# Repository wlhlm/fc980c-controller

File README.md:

Leopold FC980C Replacement Controller
=====================================

This PCB replaces the controller of the Leopold FC980C keyboard to allow running
alternate firmware, especially open source firmware such as [QMK][QMK]. This
project relies heavily on the prior reverse engineering work done by hasu (aka
tmk) and collaborators.

This is the first PCB I have designed and as such I suspect this will have many
areas that can be improved. I am very much looking forward to hearing feedback
about this design, if you think something can be improved please open an issue
and let me know. I will list my reasons for various design choices below, as
well as an errata section to list shortcomings of the current design that I am
aware of.

(the resistor hand-soldered to the connector is due to a flaw of the revision 1
design, which has been fixed in revision 2)

**Specs:**
- STM32F401 MCU as found on the Blackpill boards
- Open Hardware licensed under CERN OHL-S v2
- designed to be assembled by [JLCPCB][JLC] (can of course be manufactured
  elsewhere, but board component selection has been optimized for JLC's
  component library)

**Why would anyone want a replacement keyboard controller for the FC980C?** In
case the original controller gets fried, the lack of controller replacement from
the manufacturer would otherwise mean tossing the whole (expensive) keyboard.
This board enables the usage of Free and Open Source firmware to replace the
proprietary stock firmware. Running alternate firmware allows enabling hardware
features not accessible through the original controller such as actuation point
adjustments, not to mention the plethora of software features enabled by QMK for
example.

[QMK]: https://qmk.fm/
[JLC]: https://jlcpcb.com/

Getting started
---------------

If you have received this controller fully assembled, your next step will be
firmware setup. Check the `firmware/` directory in this repository.

In case you still have to solder on the connectors, see the assembly section
below.

Assembly
--------

This PCB is intended to be manufactured and assembled by JLCPCB, **except** for
the connectors and a button on the back of the board, which most likely have to
be soldered on the PCB by hand.

The button (labled BOOT0) is through-hole and easily soldered by hand. Make sure
to place it on the bottom side, i.e. opposite side of the MCU, where the DIP
switches are on the original controller board.

The connector for the USB board (USB) is though-hole and can be hand-soldered.

The SWD header is optional and can be left unsoldered.

The connector labeled KEYBOARD is only available for surface mounting and
unfortunately not available at JLC for assembly (at least at the time of
design). Hand-soldering is a bit more challenging for this connector. Make sure
to use a healthy dose of flux and fine gauge solder wire.

Production
----------

While the PCB itself can be manufactured by a number of PCB houses, component
selection and SMD assembly is made with [JLCPCB][JLC] in mind. The
`jlcpcb/production_files` folder for each revision should include the necessary
BOM and CPL files in addition to the Gerbers. The board parameters are specified
in the PCB design file (the main parameters being a board thickness of 1.6mm and
2 copper layers). For the option "Remove Order Number", you can select "Specify
a location".

This board is compatible with JLC's "Economic PCBA" option. For option "Assembly
Side", choose "Top Side" and under "Tooling holes" you can specify "Added by
Customer".

The EEPROM (U4) and accompanying decoupling capacitor (C6) are optional. The
board should work without those populated.

[JLC]: https://jlcpcb.com/

Design review
-------------

The specific component selection is tailored to what was available at JLCPCB at
the time of design. While things like the capacitors and resistors can be easily
substituted, Larger ICs such as the USB protection, fuse, 3.3V regulator, and
MCU have not been evaluated for alternative parts.

The USB and KEYBOARD connectors interface with the existing connectors used in
the FC980C and cannot be substituted.

I don't intend to sell this controller PCB by myself and as such everyone who is
interested in the design is meant to order this directly from JLC for
themselves. As such, I've tried to minimize cost for low quantity production
runs. JLC has the concept of extended and basic parts where the former incurs a
one-time setup fee per production rund per component as those components require
additional labor for setting up the pick and place machines with the respective
components. I've tried to keep the number of extended components as low as
possible.

### MCU

The main requirements for the microcontroller were 5V tolerance and good
compatibility with QMK. I also tried to take pricing and availability for the
foreseeable future into account. My choice fell on the STM32F401 that is used in
the cheap "Blackpill" development boards. It is well supported by QMK and is
also used in [another Topre controller board project][RFR1Replacement] that
replaces the PCB of the Realforce R1 TKL keyboards.

[RFR1Replacement]: https://github.com/Cipulot/RF_R1_8-9Xu

### Protection circuitry

The 5V fuse and USB protection components have been carried forward from the
original RP2040-based design (revision 1) and have been taken from
[this][RP2040DesignGuide] RP2040 design guide.

[RP2040DesignGuide]: https://github.com/Sleepdealr/RP2040-designguide

### USB traces

USB trace width has been calculated using the KiCad built-in calculator
following a [guide on the Digikey blog][DigikeyUSBTraceGuide]. The wide traces
are caused by the board design having two layers and a thickness of 1.6mm.  This
is most likely overkill as the bandwidth requirements are very low for a
keyboard. Reviewing a number of other boards, none were using USB-specific trace
widths.

[DigikeyUSBTraceGuide]: https://www.digikey.de/en/maker/projects/how-to-route-differential-pairs-in-kicad-for-usb/45b99011f5d34879ae1831dce1f13e93

Errata
------

### Revision 2

None found thus far.

### Revision 1

The SWD header is unusable since SWDIO has been routed to the wrong pin on the
MCU (PA15 instead of PA13). This has no impact on the actual controller
functionality. Fixed in revision 2.

Unfortunately, the `KEY_STATE` pin is missing a 5V pull-up resistor. A manual
fix (such as soldering a 10k resistor between the `KEY_STATE` \[pin 14\] and 5V
pins on the `KEYBOARD` connector) is necessary. Fixed in revision 2.

Revisions
---------

### Revision 2

Updates SWD pinout to correctly use PA13 on the MCU for SWDIO instead of PA15.

Minor position adjustments to drill holes.

Adds 5V pull-up resistor to `KEY_STATE` line.

Removes I2C level shifter to simplify BOM.

**Sample tested and working:** not yet—it is recommended to enable the options
"Confirm Production file" and "Confirm Parts Placement" when ordering from
JLC

### Revision 1

First design that has a chance to actually work in the FC980C. Switch to a
STM32F401 microcontroller. This MCU allows saving a couple of components
compared to the RP2040, such as USB termination resistors and external flash.

One notable addition compared to the previous revision is an optional 64Kb
EEPROM.

**Sample tested and working:** tested and issues identified (see Errata
section), working with the suggested manual fixes

### Revision 0

The first version of this PCB uses a RP2040 controller. Unfortunately, the
FC980C electronics rely on the MCU being 5V tolerant. I have noticed this only
while triple checking the design *just* before submitting it for manufacturing.
The RP2040 is *not* 5V tolerant and would require level shifters on many I/O
lines. Because of that I decided to scrap the design and start anew, but since
the board design was pretty much complete, I'm including it in this repository
for posterity.

**Sample tested and working:** no

Acknowledgements
----------------

This replacement controller relies heavily on the [prior reverse engineering
work][GeekhackFC980CInvestigation] of the keyboard community, including
uncovering [schematics][FC660CSchematics] for the similar Leopold FC660C that
were submitted to the FCC that helped me figure out the I/O voltage
requirements. In particular, I want to thank hasu (aka tmk) who created a FC980C
replacement controller based on the ATmega32u4 MCU, publishing schematics and an
[open source firmware implementation][TMKFC980C] for tmk that has been
[ported][QMKFC980C] to QMK.

Thanks to Toocanzs#5098 from the QMK Discord for helping me with the crystal
load capacitor calculation.

The PCB has been designed using KiCad 6 and production files have been exported
using [Bouni's JLCPCB tools plugin][BouniJLCPlugin].

[GeekhackFC980CInvestigation]: https://geekhack.org/index.php?topic=90681.0
[FC660CSchematics]: https://fccid.io/pdf.php?id=1888185
[TMKFC980C]: https://github.com/tmk/tmk_keyboard/tree/master/keyboard/fc980c
[QMKFC980C]: https://github.com/qmk/qmk_firmware/tree/f21443d6a2be8e2068164f0f3646a175ffed2df4/keyboards/fc980c
[BouniJLCPlugin]: https://github.com/Bouni/kicad-jlcpcb-tools

Resources
---------

These are various resources, that helped me designing my first PCB:

- STM AN4488 - Getting started with STM32F4xxxx MCU hardware development
- [I2C pullup recommendation by adafruit](https://learn.adafruit.com/working-with-i2c-devices/pull-up-resistors),
  [I2C pullup calculator](http://lembke.eu/arduinoablage/20201103i2cpullupcalculator/)
- [I2C Design Mathematics: Capacitance and Resistance](https://www.allaboutcircuits.com/technical-articles/i2c-design-mathematics-capacitance-and-resistance/)
- [Can an STM32 chip directly interface with a 5V I2C bus?](https://electronics.stackexchange.com/questions/50435/can-i-directly-interface-to-5v-i2c-devices-with-an-stm32-running-on-1-8v?r=SearchResults)
- [5V to 3.3V logic level translation/conversion/shifting](https://next-hack.com/index.php/2017/09/15/how-to-interface-a-5v-output-to-a-3-3v-input/)
- STM AN2867 - Oscillator design guide for STM8S, STM8A and STM32
  microcontrollers
- [Crystal capacitor guide by adafruit](https://blog.adafruit.com/2012/01/24/choosing-the-right-crystal-and-caps-for-your-design/)
- [STM32 Oscillator Calculator](https://helios.wh2.tu-dresden.de/~benni_koch/stmcalculator/)
- [Crystal Oscillator Design](https://hoani.net/posts/blog/2017-01-19-oscillator-design/)
- [Can the STM32-internal pull-up resistors be used with 5V lines?](http://forums.netduino.com/index.php?/topic/10401-guidance-using-5v-signals-with-pull-upspull-downs/)
- [KiCad differential pair routing guide by Digikey](https://www.digikey.de/en/maker/projects/how-to-route-differential-pairs-in-kicad-for-usb/45b99011f5d34879ae1831dce1f13e93)
- [RP2040 hardware design guide by Sleepdealr](https://github.com/Sleepdealr/RP2040-designguide)
- [KiCad 6 STM32 tutorial by Phil's Lab](https://www.youtube.com/watch?v=aVUqaB0IMh4)
- [KiCad PCB tutorial by MalphasWats](https://github.com/MalphasWats/hawk)
- [Layout Design Guide by Toradex](https://docs.toradex.com/102492-layout-design-guide.pdf)
- [Effective PCB Design by NXP](https://www.nxp.com/files-static/training_pdf/WBNR_PCBDESIGN.pdf)

This helped with the software matrix scanning implementation:

- [Using STM32 GPIO with ChibiOS PAL Driver](https://www.playembedded.org/blog/stm32-gpio-chibios-pal/)

This helped me immensensly in figuring out the FC980C-specific hardware
requirements for the FC980C controller:

- [FC980C pinout](https://github.com/tmk/tmk_keyboard/blob/4df8a27f7220c5f801f16151d31d4db8e563c2fa/keyboard/fc980c/README.md) by tmk
- FC660C [schematic](https://fccid.io/pdf.php?id=1888185) and [BOM](https://fccid.io/pdf.php?id=1888184)

License
-------

Copyright © 2022 Wilhelm Schuster

This PCB design is licensed under the CERN-OHL-S v2. See the LICENSE file in
each of the revision folders for the license text. This license is strongly
reciprocal and is similar in spirit to the GPL, but specifically focuses on
hardware.

The firmware portion of this project is licensed under GPL-2-or-later in
accordance with the QMK project. See the LICENSE file in the firmware folder for
the license text.

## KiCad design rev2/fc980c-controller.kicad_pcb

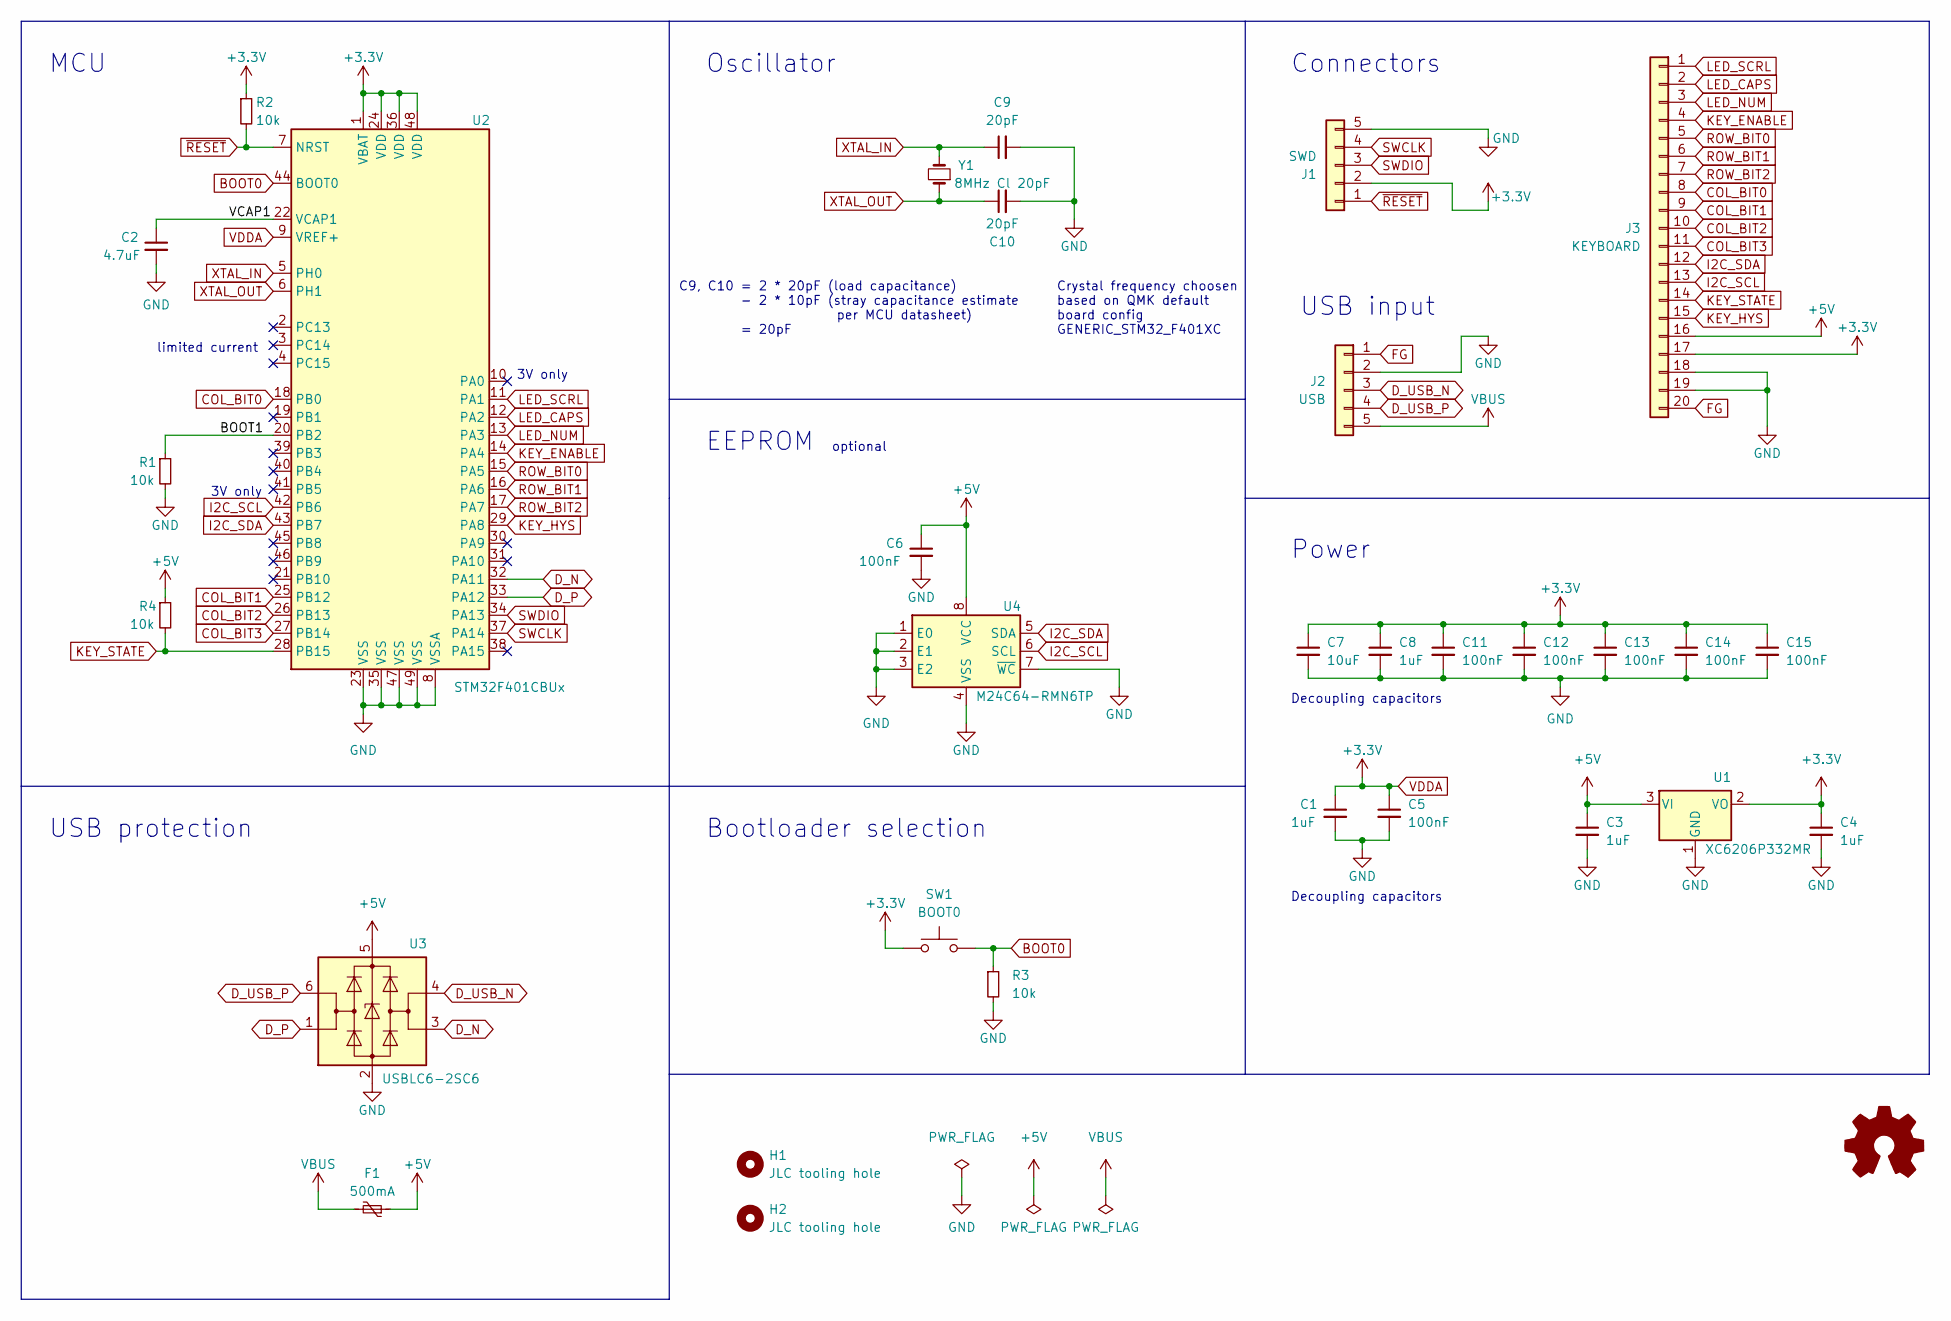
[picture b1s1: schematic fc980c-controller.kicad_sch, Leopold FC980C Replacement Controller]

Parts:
C1: 1uF; C_0402_1005Metric
C2: 4.7uF; C_0603_1608Metric
C3, C4, C8: 1uF; C_0603_1608Metric
C5, C6, C11, C12, C13, C14, C15: 100nF; C_0402_1005Metric
C7: 10uF; C_0603_1608Metric
C9, C10: 20pF; C_0402_1005Metric
F1: 500mA; Fuse_1206_3216Metric
H1, H2: JLC tooling hole; JLC_tooling_hole
J1: SWD; PinHeader_1x05_P2.54mm_Horizontal
J2: USB; JST_PH_S5B-PH-K_1x05_P2.00mm_Horizontal
J3: KEYBOARD; HRS_DF14_20P
LOGO1: Logo_Open_Hardware_Small; OSHW-Logo2_7.3x6mm_SilkScreen
R1, R2, R3, R4: 10k; R_0402_1005Metric
SW1: BOOT0; SW_PUSH_6mm
U1: XC6206P332MR; SOT-23
U2: STM32F401CBUx; QFN-48-1EP_7x7mm_P0.5mm_EP5.6x5.6mm
U3: USBLC6-2SC6; SOT-23-6
U4: M24C64-RMN6TP; SOIC-8_3.9x4.9mm_P1.27mm
Y1: 8MHz Cl 20pF; Crystal_SMD_5032-2Pin_5.0x3.2mm

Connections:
+5V: C3.1, C6.1, F1.1, J3.16, R4.1, U1.3 (VI), U3.5 (VBUS), U4.8 (VCC)
/BOOT1: R1.1, U2.20 (PB2)
/VCAP1: C2.1, U2.22 (VCAP1)
BOOT0: R3.1, SW1.2, U2.44 (BOOT0)
COL_BIT0: J3.8, U2.18 (PB0)
COL_BIT1: J3.9, U2.25 (PB12)
COL_BIT2: J3.10, U2.26 (PB13)
COL_BIT3: J3.11, U2.27 (PB14)
D_N: U2.32 (PA11), U3.3 (I/O2)
D_P: U2.33 (PA12), U3.1 (I/O1)
D_USB_N: J2.3, U3.4 (I/O2)
D_USB_P: J2.4, U3.6 (I/O1)
FG: J2.1, J3.20
GND: C1.2, C2.2, C3.2, C4.2, C5.2, C6.2, C7.2, C8.2, C9.2, C10.2, C11.2, C12.2, C13.2, C14.2, C15.2, J1.5, J2.2, J3.18, J3.19, J3.21, J3.22, R1.2, R3.2, U1.1 (GND), U2.8 (VSSA), U2.23 (VSS), U2.35 (VSS), U2.47 (VSS), U2.49 (VSS), U3.2 (GND), U4.1 (E0), U4.2 (E1), U4.3 (E2), U4.4 (VSS), U4.7 (~WC)
I2C_SCL: J3.13, U2.42 (PB6), U4.6 (SCL)
I2C_SDA: J3.12, U2.43 (PB7), U4.5 (SDA)
KEY_ENABLE: J3.4, U2.14 (PA4)
KEY_HYS: J3.15, U2.29 (PA8)
KEY_STATE: J3.14, R4.2, U2.28 (PB15)
LED_CAPS: J3.2, U2.12 (PA2)
LED_NUM: J3.3, U2.13 (PA3)
LED_SCRL: J3.1, U2.11 (PA1)
ROW_BIT0: J3.5, U2.15 (PA5)
ROW_BIT1: J3.6, U2.16 (PA6)
ROW_BIT2: J3.7, U2.17 (PA7)
SWCLK: J1.4, U2.37 (PA14)
SWDIO: J1.3, U2.34 (PA13)
VBUS: F1.2, J2.5
VDDA: C1.1, C4.1, C5.1, C7.1, C8.1, C11.1, C12.1, C13.1, C14.1, C15.1, J1.2, J3.17, R2.1, SW1.1, U1.2 (VO), U2.1 (VBAT), U2.9 (VREF+), U2.24 (VDD), U2.36 (VDD), U2.48 (VDD)
XTAL_IN: C9.1, U2.5 (PH0), Y1.2
XTAL_OUT: C10.1, U2.6 (PH1), Y1.1
~RESET: J1.1, R2.2, U2.7 (NRST)

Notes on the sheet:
Decoupling capacitors
3V only
Oscillator
C9, C10 = 2 * 20pF (load capacitance) - 2 * 10pF (stray capacitance estimate per MCU datasheet) = 20pF
Power
limited current
Bootloader selection
Connectors
Crystal frequency choosen based on QMK default board config GENERIC_STM32_F401XC
USB input
USB protection
optional
MCU
EEPROM

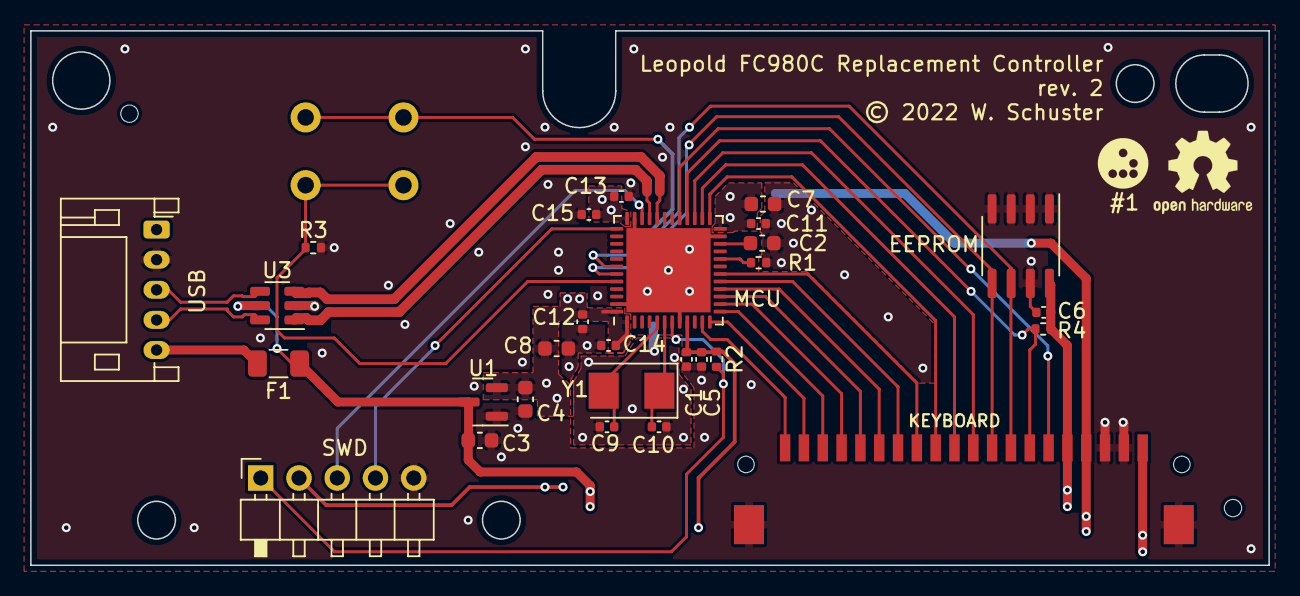
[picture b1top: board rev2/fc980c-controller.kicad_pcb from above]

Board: 2 copper layers, 82.2 x 35.5 mm, 32 parts (1 on the bottom side), 32 nets.

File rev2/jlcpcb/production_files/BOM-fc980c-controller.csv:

Comment,Designator,Footprint,LCSC
8MHz Cl 20pF,Y1,Crystal_SMD_5032-2Pin_5.0x3.2mm,C115962
STM32F401CBUx,U2,QFN-48-1EP_7x7mm_P0.5mm_EP5.6x5.6mm,C118825
100nF,"C11,C12,C13,C14,C15,C5,C6",C_0402_1005Metric,C1525
20pF,"C10,C9",C_0402_1005Metric,C1554
USB,J2,JST_PH_S5B-PH-K_1x05_P2.00mm_Horizontal,C157923
1uF,"C3,C4,C8",C_0603_1608Metric,C15849
4.7uF,C2,C_0603_1608Metric,C19666
10uF,C7,C_0603_1608Metric,C19702
10k,"R1,R2,R3,R4",R_0402_1005Metric,C25744
USBLC6-2SC6,U3,SOT-23-6,C2827654
BOOT0,SW1,SW_PUSH_6mm,C2834895
KEYBOARD,J3,HRS_DF14_20P,C506679
1uF,C1,C_0402_1005Metric,C52923
XC6206P332MR,U1,SOT-23,C5446
500mA,F1,Fuse_1206_3216Metric,C70076
M24C64-RMN6TP,U4,SOIC-8_3.9x4.9mm_P1.27mm,C79988
SWD,J1,PinHeader_1x05_P2.54mm_Horizontal,

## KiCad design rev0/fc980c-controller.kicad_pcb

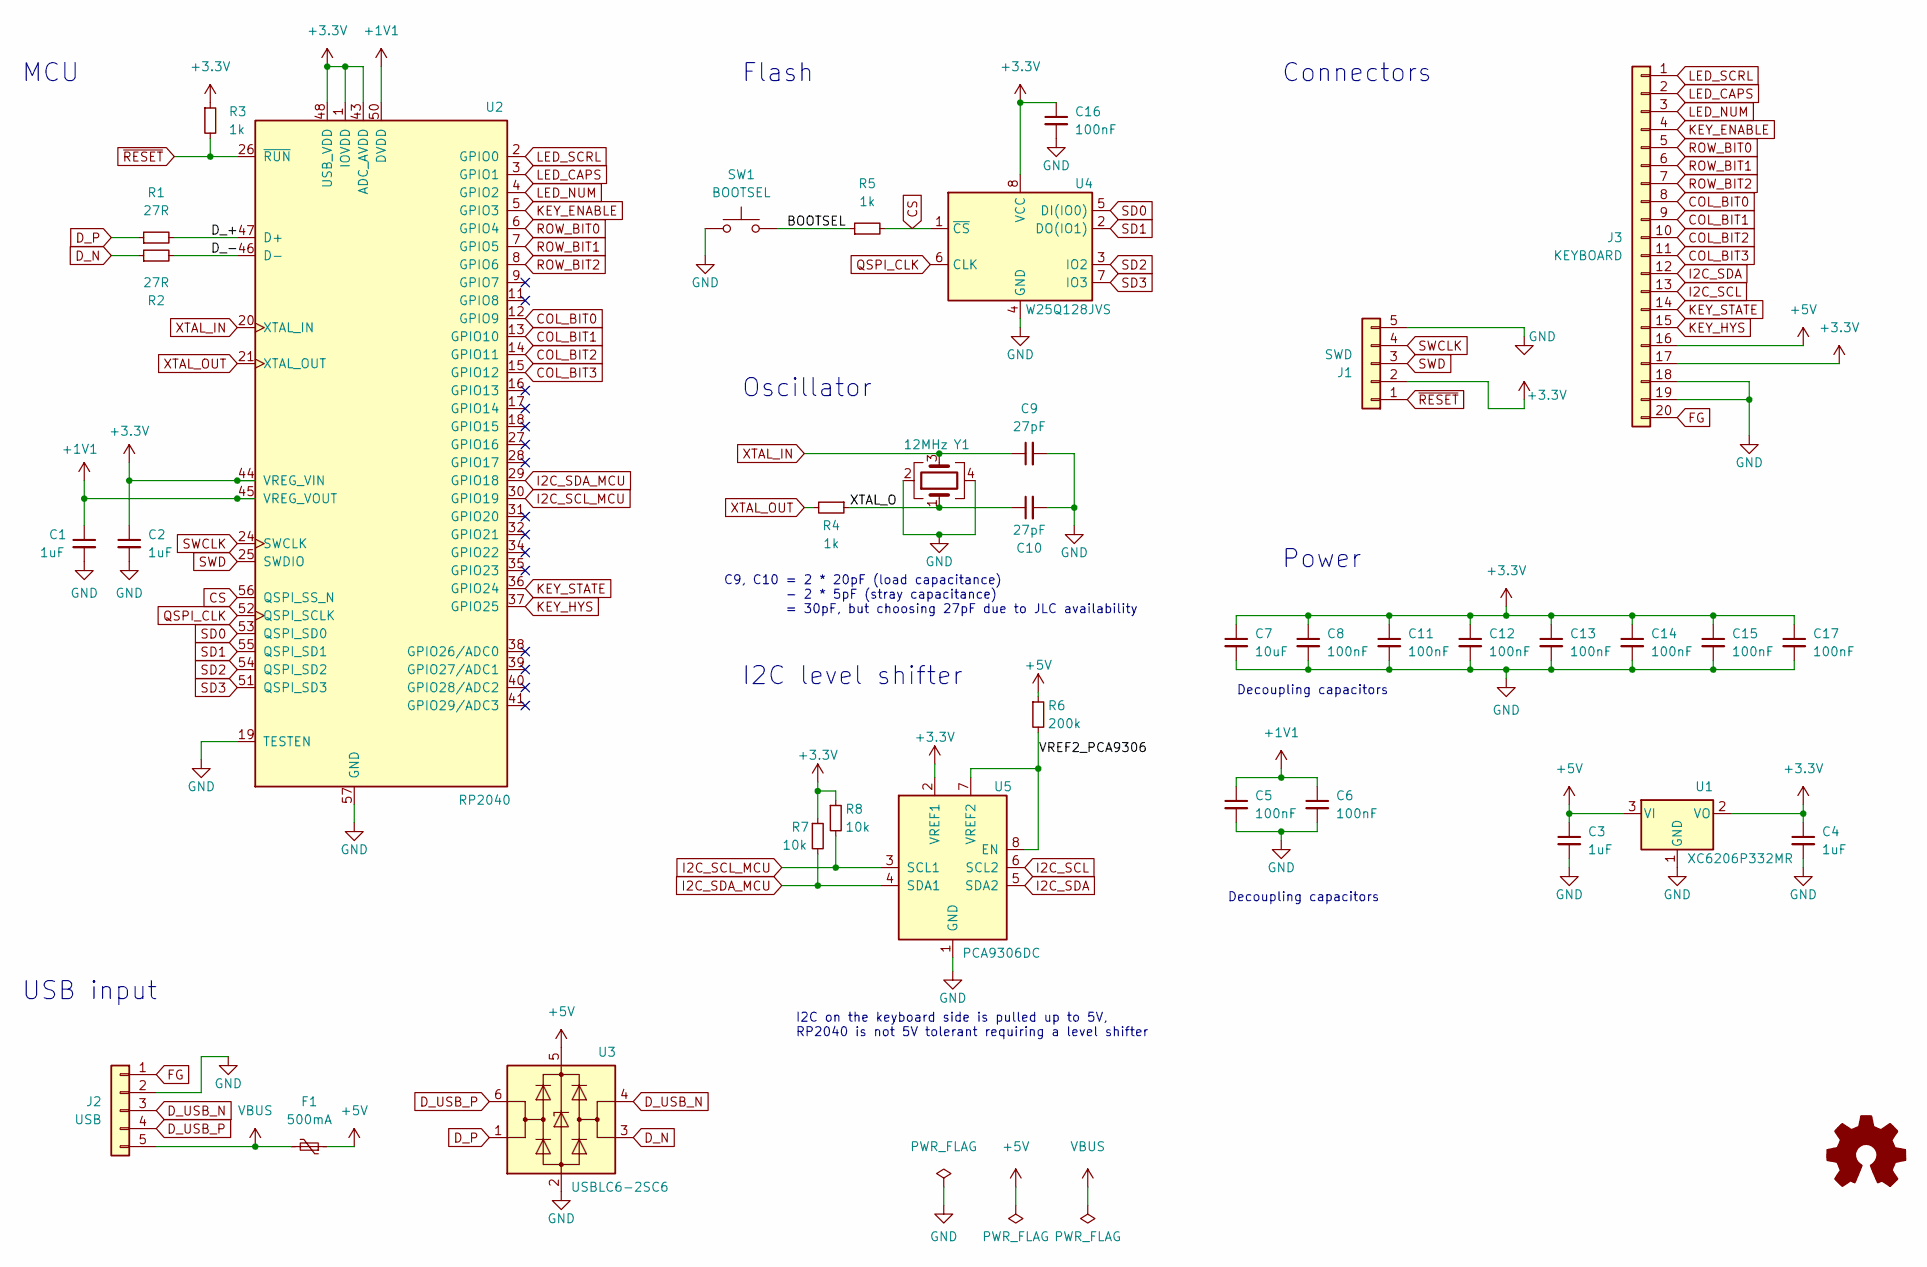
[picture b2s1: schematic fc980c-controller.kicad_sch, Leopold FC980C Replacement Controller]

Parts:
C1, C2, C3, C4: 1uF; C_0402_1005Metric
C5, C6, C8, C11, C12, C13, C14, C15, C16, C17: 100nF; C_0402_1005Metric
C7: 10uF; C_0603_1608Metric
C9, C10: 27pF; C_0402_1005Metric
F1: 500mA; Fuse_1206_3216Metric
J1: SWD; PinHeader_1x05_P2.54mm_Horizontal
J2: USB; JST_PH_S5B-PH-SM4-TB_1x05-1MP_P2.00mm_Horizontal
J3: KEYBOARD; HRS_DF14_20P
LOGO1: Logo_Open_Hardware_Small; OSHW-Logo2_7.3x6mm_SilkScreen
R1, R2: 27R; R_0402_1005Metric
R3, R4, R5: 1k; R_0402_1005Metric
R6: 200k; R_0402_1005Metric
R7, R8: 10k; R_0402_1005Metric
SW1: BOOTSEL; SW_PUSH_6mm
U1: XC6206P332MR; SOT-23
U2: RP2040; RP2040-QFN-56
U3: USBLC6-2SC6; SOT-23-6
U4: W25Q128JVS; SOIC-8_5.23x5.23mm_P1.27mm
U5: PCA9306DC; VSSOP-8_2.3x2mm_P0.5mm
Y1: 12MHz; Crystal_SMD_3225-4Pin_3.2x2.5mm

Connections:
+1V1: C1.1, C5.1, C6.1, U2.23 (DVDD), U2.45 (VREG_VOUT), U2.50 (DVDD)
+3.3V: C2.1, C4.1, C7.1, C8.1, C11.1, C12.1, C13.1, C14.1, C15.1, C16.1, C17.1, J1.2, J3.17, R3.1, R7.1, R8.1, U1.2 (VO), U2.1 (IOVDD), U2.10 (IOVDD), U2.22 (IOVDD), U2.33 (IOVDD), U2.42 (IOVDD), U2.43 (ADC_AVDD), U2.44 (VREG_VIN), U2.48 (USB_VDD), U2.49 (IOVDD), U4.8 (VCC), U5.2 (VREF1)
+5V: C3.1, F1.1, J3.16, R6.1, U1.3 (VI), U3.5 (VBUS)
/BOOTSEL: R5.1, SW1.2
/D_+: R1.2, U2.47 (D+)
/D_-: R2.2, U2.46 (D-)
/VREF2_PCA9306: R6.2, U5.7 (VREF2), U5.8 (EN)
/XTAL_O: C10.1, R4.1, Y1.1
COL_BIT0: J3.8, U2.12 (GPIO9)
COL_BIT1: J3.9, U2.13 (GPIO10)
COL_BIT2: J3.10, U2.14 (GPIO11)
COL_BIT3: J3.11, U2.15 (GPIO12)
CS: R5.2, U2.56 (QSPI_SS_N), U4.1 (~CS)
D_N: R2.1, U3.3 (I/O2)
D_P: R1.1, U3.1 (I/O1)
D_USB_N: J2.3, U3.4 (I/O2)
D_USB_P: J2.4, U3.6 (I/O1)
FG: J2.1, J3.20
GND: C1.2, C2.2, C3.2, C4.2, C5.2, C6.2, C7.2, C8.2, C9.2, C10.2, C11.2, C12.2, C13.2, C14.2, C15.2, C16.2, C17.2, J1.5, J2.2, J3.18, J3.19, SW1.1, U1.1 (GND), U2.19 (TESTEN), U2.57 (GND), U3.2 (GND), U4.4 (GND), U5.1 (GND), Y1.2, Y1.4
I2C_SCL: J3.13, U5.6 (SCL2)
I2C_SCL_MCU: R8.2, U2.30 (GPIO19), U5.3 (SCL1)
I2C_SDA: J3.12, U5.5 (SDA2)
I2C_SDA_MCU: R7.2, U2.29 (GPIO18), U5.4 (SDA1)
KEY_ENABLE: J3.4, U2.5 (GPIO3)
KEY_HYS: J3.15, U2.37 (GPIO25)
KEY_STATE: J3.14, U2.36 (GPIO24)
LED_CAPS: J3.2, U2.3 (GPIO1)
LED_NUM: J3.3, U2.4 (GPIO2)
LED_SCRL: J3.1, U2.2 (GPIO0)
QSPI_CLK: U2.52 (QSPI_SCLK), U4.6 (CLK)
ROW_BIT0: J3.5, U2.6 (GPIO4)
ROW_BIT1: J3.6, U2.7 (GPIO5)
ROW_BIT2: J3.7, U2.8 (GPIO6)
SD0: U2.53 (QSPI_SD0), U4.5 (DI(IO0))
SD1: U2.55 (QSPI_SD1), U4.2 (DO(IO1))
SD2: U2.54 (QSPI_SD2), U4.3 (IO2)
SD3: U2.51 (QSPI_SD3), U4.7 (IO3)
SWCLK: J1.4, U2.24 (SWCLK)
SWD: J1.3, U2.25 (SWDIO)
VBUS: F1.2, J2.5
XTAL_IN: C9.1, U2.20 (XTAL_IN), Y1.3
XTAL_OUT: R4.2, U2.21 (XTAL_OUT)
~RESET: J1.1, R3.2, U2.26 (~RUN)

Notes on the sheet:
Oscillator
I2C level shifter
C9, C10 = 2 * 20pF (load capacitance) - 2 * 5pF (stray capacitance) = 30pF, but choosing 27pF due to JLC availability
Power
Decoupling capacitors
Connectors
Flash
I2C on the keyboard side is pulled up to 5V, RP2040 is not 5V tolerant requiring a level shifter
USB input
MCU

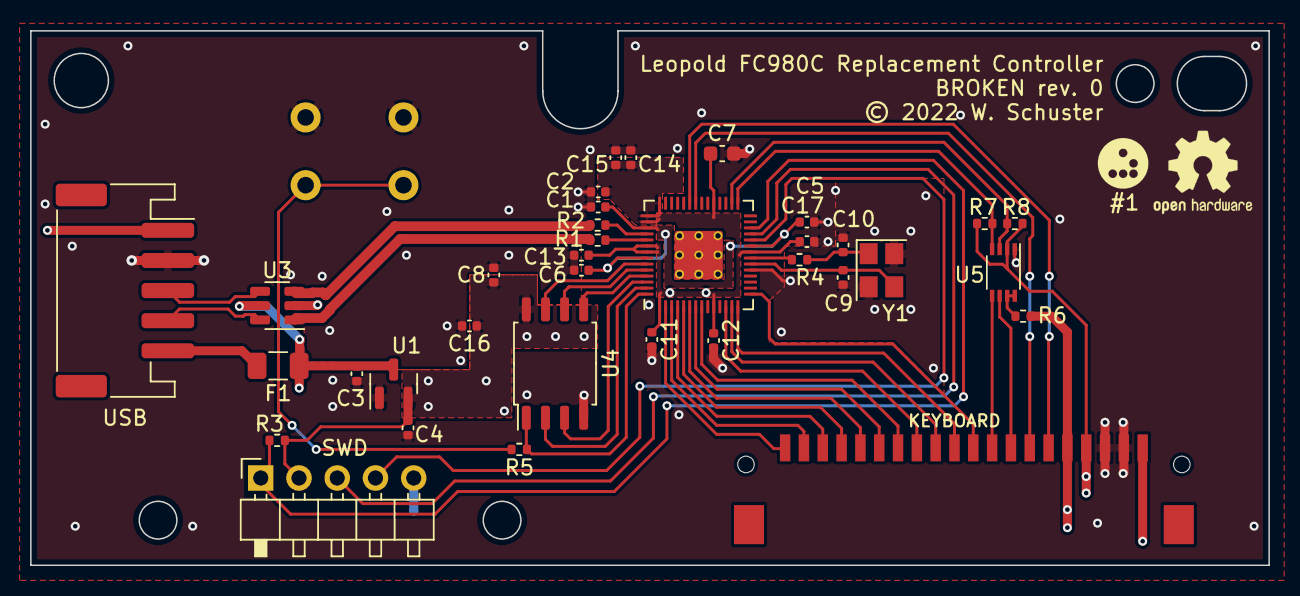
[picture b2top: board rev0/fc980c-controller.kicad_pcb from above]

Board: 2 copper layers, 82.2 x 35.5 mm, 37 parts (1 on the bottom side), 43 nets.

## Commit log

2022-12-18 rev1: Add EEPROM
    This should alleviate needing to use MCU flash for EEPROM emulation.
    Also recalculate crystal load capacitor values using guidance from the
    MCU datasheet.
2022-12-18 rev1: Small tweaks after test submitting to JLC
    Fix some component rotations and tweak top GND copper zone near the
    edge.
2022-12-18 README: 80 column reformat
2022-12-20 rev1: Minor tweaks before first production run
    Most notably change to a capacitor footprint rather than resistor
    footprint for C6.
    Small via tweaks.
    Adjust component rotations reviewing JLC SMTA preview. (still waiting on
    JLC review at this point)
2022-12-20 Adjust gitignore for files generated by the KiCad JLC plugin
2022-12-22 rev1: Final production files for first run
    Last tweak is to add tooling holes necessary for JLC PCB assembly. JLC
    will place them on their own, however in their first attempt put one
    hole over the silkscreen, so placing them manually should prevent this
    in the future.
2023-01-02 rev2: Fix SWDIO MCU pin
    Didn't take long to find flaws in the revision 1 design. SWDIO is
    erroneously hooked up to PA15 on the MCU instead of PA13.
2023-01-02 rev2: Explain oscillator frequency choice
2023-01-02 rev2: Update revision references in schematic and PCB
2023-01-02 rev2: Minor position adjustment to mounting drill holes
2023-01-03 Move link around in README
2023-01-06 rev2: Copy files to new directory
2023-01-06 rev1: Revert rev2 changes
2023-01-06 rev2: Add 5V pull-up to KEY_STATE pin
2023-01-06 rev2: Drop I2C level shifter
    Upon further review, using a 5V I2C bus should be unproblematic with a
    5V tolerant MCU due to the open-drain design.
2023-01-08 Remove mentions of the I2C level shifter from README
2023-01-08 rev2: Exclude some components from BOM
2023-01-08 rev2: Add "MCU" silkscreen
2023-01-08 rev2: Rotate SWD header 3D model
2023-01-08 Add rev2 render to README
2023-01-08 rev2: Add schematic PDF export
2023-01-08 firmware: Add license file and README
2023-01-08 Add initial QMK firmware config
2023-01-08 Mention why a replacement controller makes sense
2023-01-08 firmware: Add premade binaries
2023-01-08 firmware: Replace tabs with spaces
2023-01-08 firmware: Drop stray commas in keymaps
2023-01-08 Mention more helpful resources in README
2023-01-08 Add license file to sleep-lib
2023-01-08 rev2: Add production files
2023-01-08 Add photos of prototype rev1 PCB
2023-01-08 firmware: Fix README make example command
2023-01-08 Fix image links in README
2023-01-08 Clarify production notes
2023-01-08 Reword README
2023-01-08 Fix typos and reword README
2023-01-28 firmware: Disable console by default
2023-01-28 firmware: README and code comment rewording
2023-01-28 firmware: Save AP_RST to EEPROM
2023-01-28 firmware: Update precompiled firmware
2023-01-28 firmware: Reword README
2023-01-28 firmware: Add render to QMK README
2023-01-30 firmware: Replace uprintf with dprintf
2023-01-30 firmware: Revise comments and READMEs
2023-01-30 firmware: Drop config_common.h include
2023-02-02 firmware: Update copyright year
2024-08-15 firmware: Update QMK to 0.25.x
2024-08-15 firmware: Move actuation_point.h include around
2024-08-15 firmware: Migrate bootmagic lite to info.json
2024-08-15 firmware: Update QMK GPIO API
2024-08-15 firmware: Define bootmagic and EEPROM driver in info.json
2024-08-15 firmware: Rename info.json to keyboard.json
2024-08-15 firmware: Update QMK I2C API
2024-08-15 firmware: Update README
2024-08-15 firmware: Update firmware binaries
2024-08-17 firmware: Use correct format specifiers for actuation_point API
2024-09-09 rev2: Fix typo in schematic

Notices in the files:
rev0/fc980c-controller.kicad_pcb:
© 2022 W. Schuster
